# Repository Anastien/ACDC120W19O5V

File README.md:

19.5V 120W Universal Input AC Power Supply.

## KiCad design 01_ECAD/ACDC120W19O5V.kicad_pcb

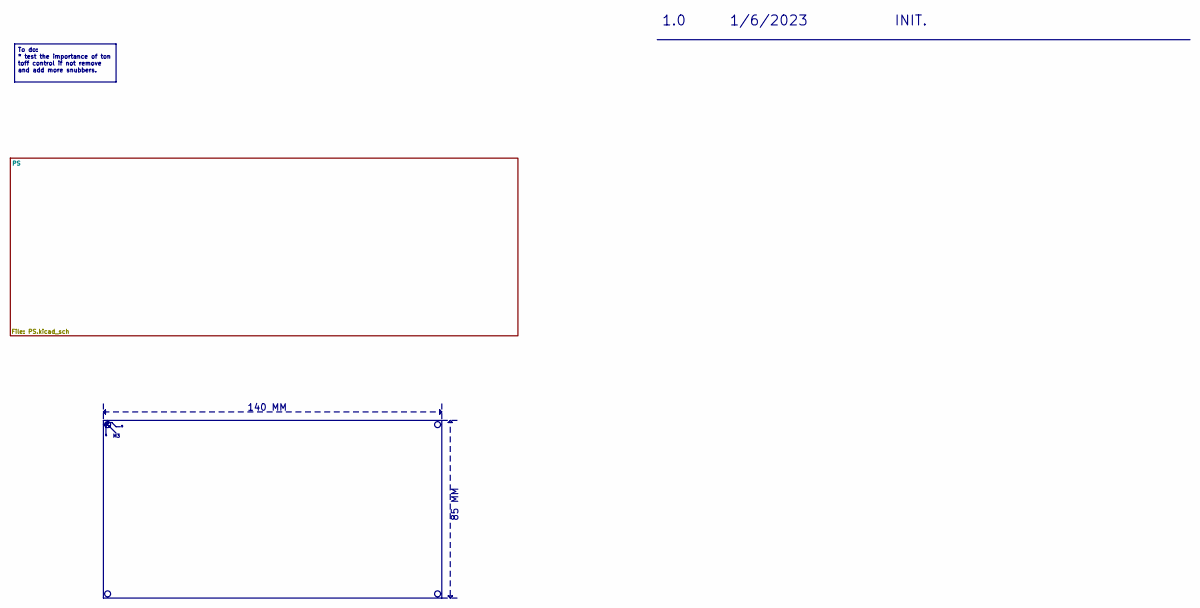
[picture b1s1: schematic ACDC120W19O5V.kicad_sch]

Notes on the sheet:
85 MM
1/6/2023
140 MM
1.0
INIT.
To do: * test the importance of ton toff control if not remove and add more snubbers.

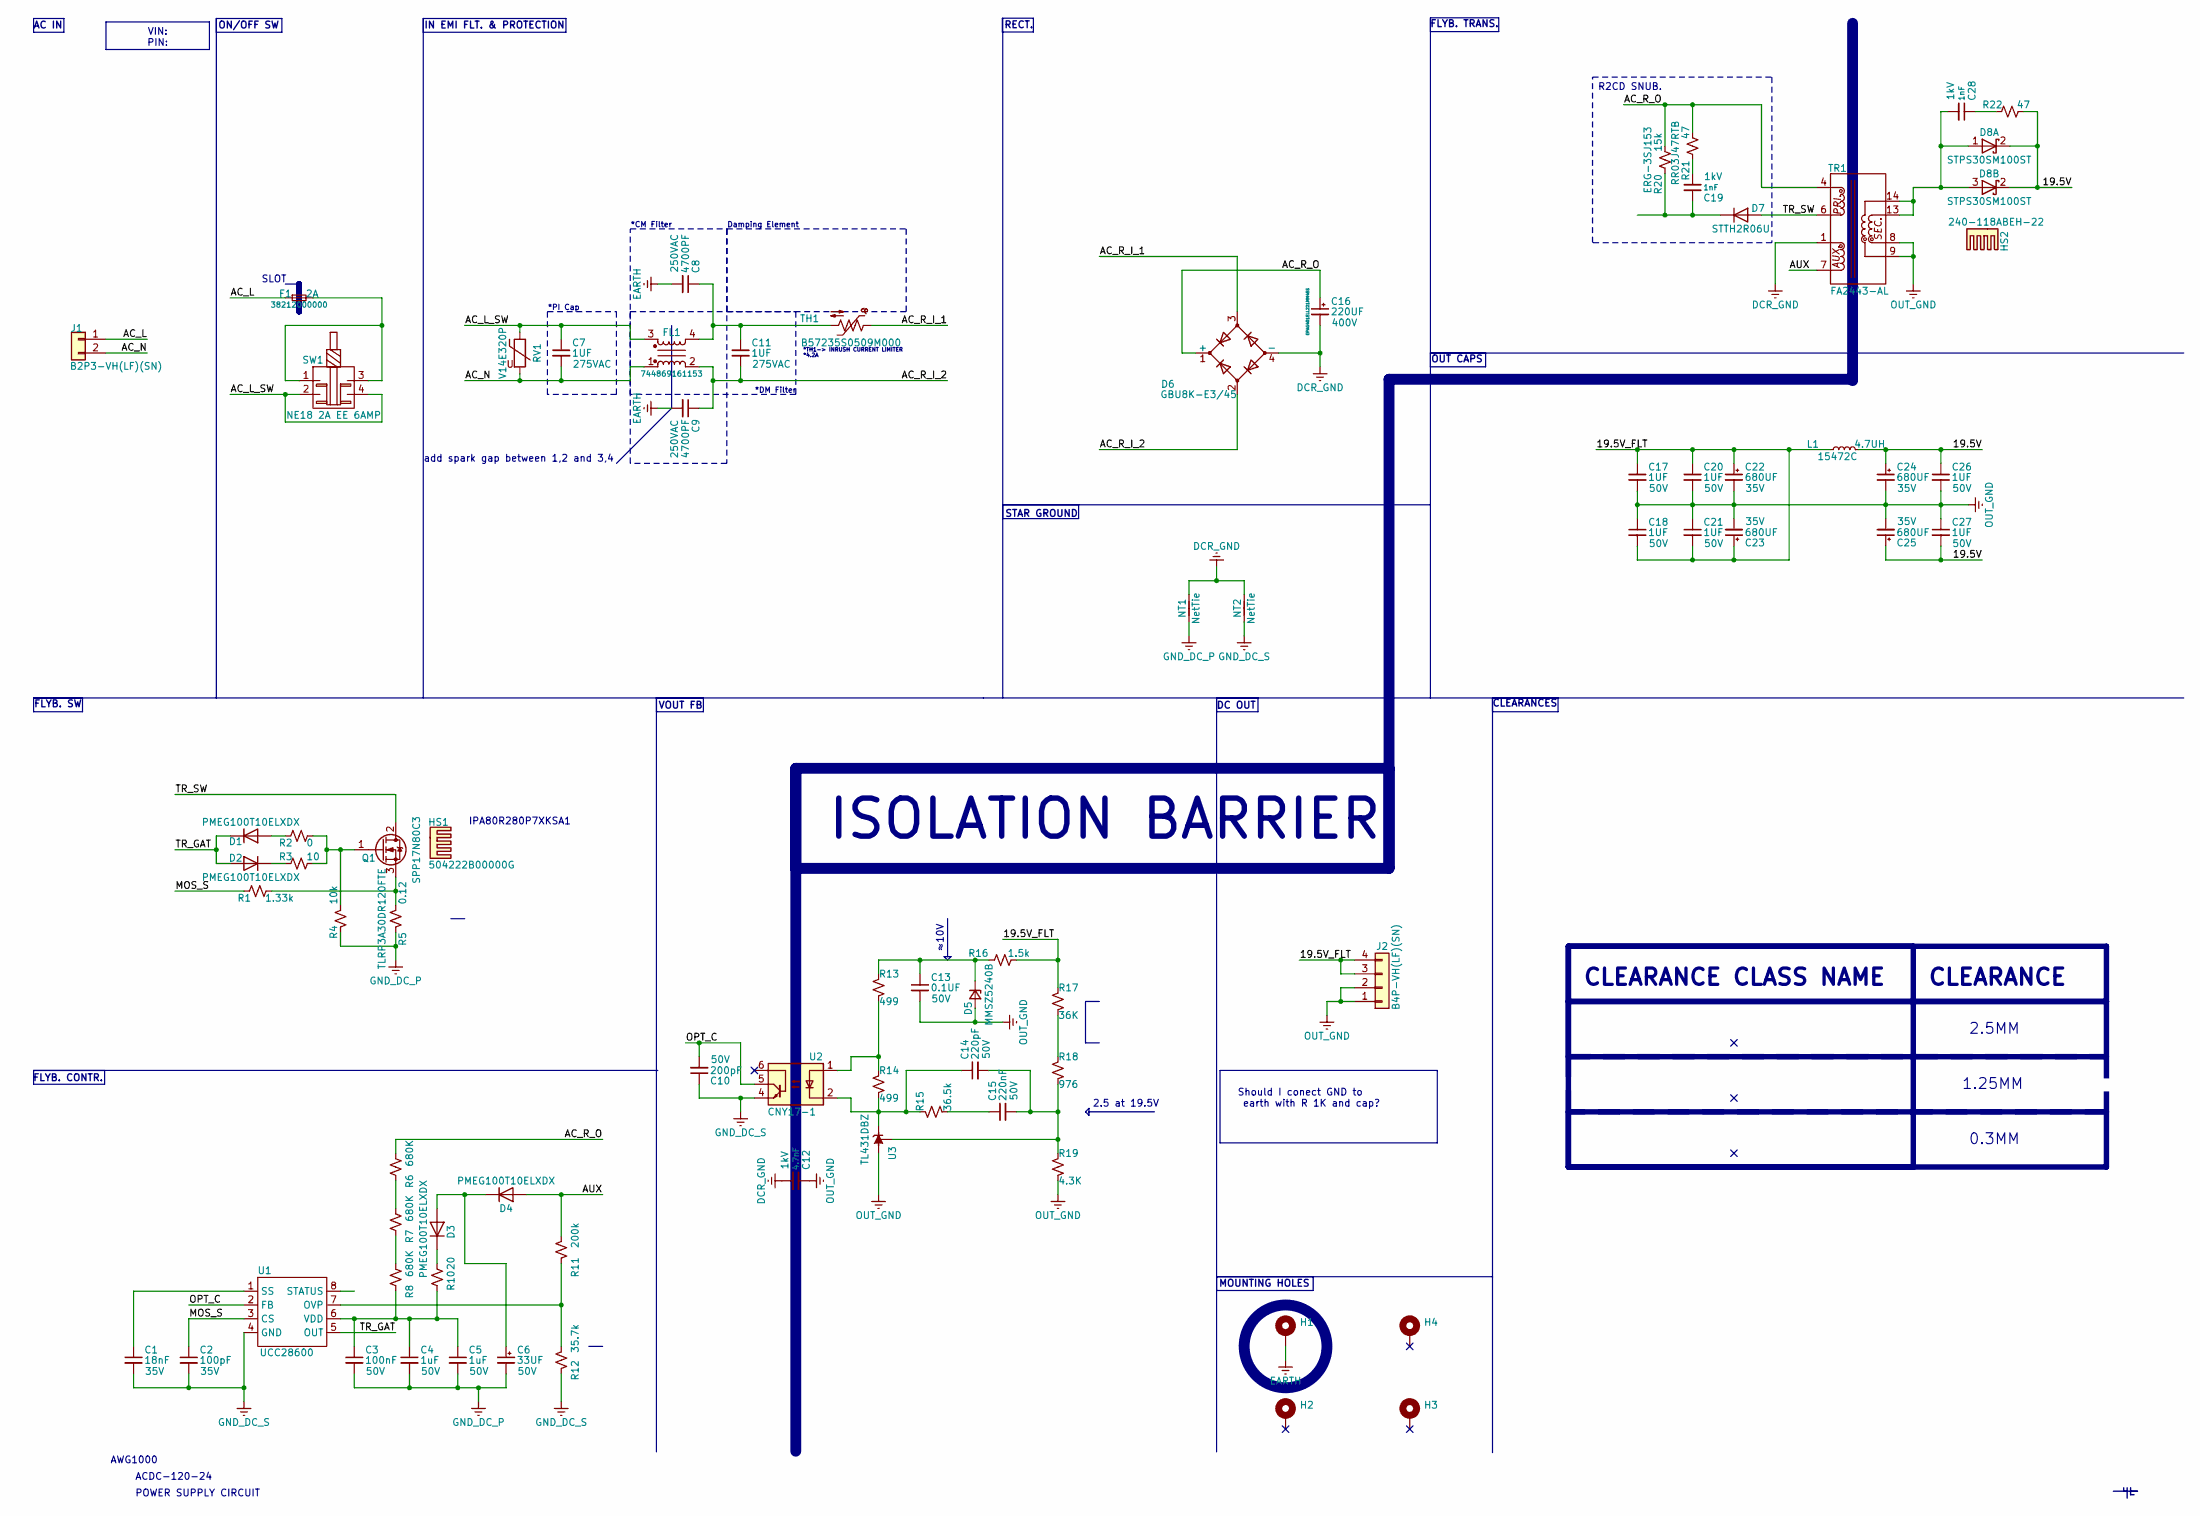
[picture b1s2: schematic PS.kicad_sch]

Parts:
C1: 18nF; C_0603_1608Metric; VOLTAGE 35V
C2: 100pF; C_0603_1608Metric; VOLTAGE 35V
C3: 100nF; C_0603_1608Metric; VOLTAGE 50V
C4, C5: 1uF; C_0603_1608Metric; VOLTAGE 50V
C6: 33UF; C_Radial_D6.3mm_H11.0mm_P2.50mm; VOLTAGE 50V
C7, C11: 1UF; 890324026027CS; VOLTAGE 275VAC
C8, C9: 4700PF; C_Disc_D10.5mm_W5.0mm_P5.00mm; VOLTAGE 250VAC
C10: 200pF; C_0603_1608Metric; VOLTAGE 50V
C12: 4.7nF; C_Disc_D7.5mm_W5.0mm_P7.50mm; VOLTAGE 1kV
C13: 0.1UF; C_0603_1608Metric; VOLTAGE 50V
C14: 220pF; C_0603_1608Metric; VOLTAGE 50V
C15: 220nF; C_0603_1608Metric; VOLTAGE 50V
C16: 220UF; CP_Radial_D18.0mm_P7.50mm; VOLTAGE 400V
C17, C18, C20, C21, C26, C27: 1UF; C_0805_2012Metric_Pad1.18x1.45mm_HandSolder; VOLTAGE 50V
C19, C28: 1nF; C_Disc_D7.5mm_W5.0mm_P7.50mm; VOLTAGE 1kV
C22, C23, C24, C25: 680UF; EKZN630ELL681MK30S; VOLTAGE 35V
D1, D2, D3, D4: PMEG100T10ELXDX; D_SOD-323
D5: MMSZ5240B; D_SOD-123F
D6: GBU8K-E3/45; Diode_Bridge_Vishay_GBU
D7: STTH2R06U; D_SMB
D8: STPS30SM100ST; TO-220-3-240
F1: 38212000000; 38211000410; Current Rating 2A
FL1: 744869161153
H1, H2, H3, H4: MountingHole_Pad; MountingHole_3.2mm_M3_DIN965_Pad_TopBottom
HS1: 504222B00000G
HS2: 240-118ABEH-22
J1: B2P3-VH(LF)(SN); JST_VH_B2P3-VH_1x02_P7.92mm_Vertical
J2: B4P-VH(LF)(SN); JST_VH_B4P-VH-B_1x04_P3.96mm_Vertical
L1: 4.7UH; 744750340047
NT1: NetTie; NetTie-2_SMD_Pad2.0mm
NT2: NetTie; NetTie-2_SMD_Pad0.5mm
Q1: SPP17N80C3; TO-220-3-240
R1: 1.33k; R_0603_1608Metric
R2: 0; R_0603_1608Metric
R3: 10; R_0603_1608Metric
R4: 10k; R_0603_1608Metric
R5: 0.12; R_2512_6332Metric_Pad1.40x3.35mm_HandSolder
R6, R7, R8: 680K; R_1206_3216Metric_Pad1.30x1.75mm_HandSolder
R10: 20; R_0603_1608Metric
R11: 200k; R_0603_1608Metric
R12: 35.7k; R_0603_1608Metric
R13, R14: 499; R_0603_1608Metric
R15: 36.5k; R_0603_1608Metric
R16: 1.5k; R_0603_1608Metric
R17: 36K; R_0603_1608Metric
R18: 976; R_0603_1608Metric
R19: 4.3K; R_0603_1608Metric
R20: 15k; R_Axial_DIN0516_L15.5mm_D5.0mm_P5.08mm_Vertical
R21, R22: 47; R_Axial_DIN0516_L15.5mm_D5.0mm_P5.08mm_Vertical
RV1: V14E320P; RV_Disc_D16.5mm_W6.7mm_P7.5mm
SW1: NE18 2A EE 6AMP; NE1846EE
TH1: B57235S0509M000; RV_Disc_D9mm_W6.1mm_P5mm
TR1: FA2443-AL
U1: UCC28600; SOIC-8_3.9x4.9mm_P1.27mm
U2: CNY17-1; DIP-6_W7.62mm_LongPads
U3: TL431DBZ; SOT-23

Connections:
/PS/19.5V: C24.1, C25.1, C26.1, C27.2, D8.2 (K), L1.2, R22.2
/PS/19.5V_FLT: C17.1, C18.2, C20.1, C21.2, C22.1, C23.1, J2.3, J2.4, L1.1, R16.2, R17.2
/PS/AC_L: F1.1, J1.1
/PS/AC_L_SW: C7.1, FL1.3, RV1.1, SW1.2, SW1.4
/PS/AC_N: C7.2, FL1.1, J1.2, RV1.2
/PS/AC_R_I_1: D6.3, TH1.1
/PS/AC_R_I_2: C9.1, C11.2, D6.2, FL1.2
/PS/AC_R_O: C16.1, D6.1 (+), R6.2, R20.2, R21.2, TR1.4
/PS/AUX: D4.2 (A), R11.2, TR1.7
/PS/MOS_S: C2.1, R1.2, U1.3 (CS)
/PS/OPT_C: C10.2, U1.2 (FB), U2.5
/PS/TR_GAT: D1.1 (K), D2.2 (A), U1.5 (OUT)
/PS/TR_SW: D7.2 (A), Q1.2 (D), TR1.6
DCR_GND: C12.2, C16.2, D6.4 (-), NT1.2, NT2.2, TR1.1
EARTH: C8.2, C9.2, H1.1
GND_DC_P: C3.2, C4.2, C5.2, C6.2, NT1.1, R4.2, R5.2
GND_DC_S: C1.2, C2.2, C10.1, NT2.1, R12.2, U1.4 (GND), U2.4
unnamed: C8.1, C11.1, FL1.4, TH1.2
unnamed: C15.1, R15.1
unnamed: C19.2, R21.1
unnamed: C28.1, R22.1
unnamed: D1.2 (A), R2.2
unnamed: D2.1 (K), R3.2
unnamed: C6.1, D3.2 (A), D4.1 (K)
unnamed: D3.1 (K), R10.1
unnamed: C13.1, D5.1 (K), R13.2, R16.1
unnamed: C19.1, D7.1 (K), R20.1
unnamed: C28.2, D8.1 (A), D8.3 (K), TR1.13, TR1.14
unnamed: F1.2, SW1.1, SW1.3
unnamed: Q1.1 (G), R2.1, R3.1, R4.1
unnamed: Q1.3 (S), R1.1, R5.1
unnamed: R6.1, R7.2
unnamed: R7.1, R8.2
unnamed: R13.1, R14.2, U2.1
unnamed: R17.1, R18.2
unnamed: R11.1, R12.1, U1.7 (OVP)
unnamed: C1.1, U1.1 (SS)
unnamed: C3.1, C4.1, C5.1, R8.1, R10.2, U1.6 (VDD)
unnamed: C14.1, R14.1, R15.2, U2.2, U3.1 (K)
unnamed: C14.2, C15.2, R18.1, R19.2, U3.2 (REF)
OUT_GND: C12.1, C13.2, C17.2, C18.1, C20.2, C21.1, C22.2, C23.2, C24.2, C25.2, C26.2, C27.1, D5.2 (A), J2.1, J2.2, R19.1, TR1.8, TR1.9, U3.3 (A)

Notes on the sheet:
CLEARANCE CLASS NAME
MOUNTING HOLES
2.5MM
OUT CAPS
RECT.
VOUT FB
POWER SUPPLY CIRCUIT
IN EMI FLT. & PROTECTION
AC IN
1.25MM
CLEARANCE
2.5 at 19.5V
*PI Cap
Damping Element
add spark gap between 1,2 and 3,4
FLYB. CONTR.
*4.2A
CLEARANCES
≈10V
IPA80R280P7XKSA1
AWG1000
*CM Filter
Should I conect GND to earth with R 1K and cap?
FLYB. TRANS.
ACDC-120-24
*DM Filter
*TH1-> INRUSH CURRENT LIMITER
DC OUT
STAR GROUND
ON/OFF SW
ISOLATION BARRIER
0.3MM
FLYB. SW
SLOT
R2CD SNUB.
VIN: PIN:

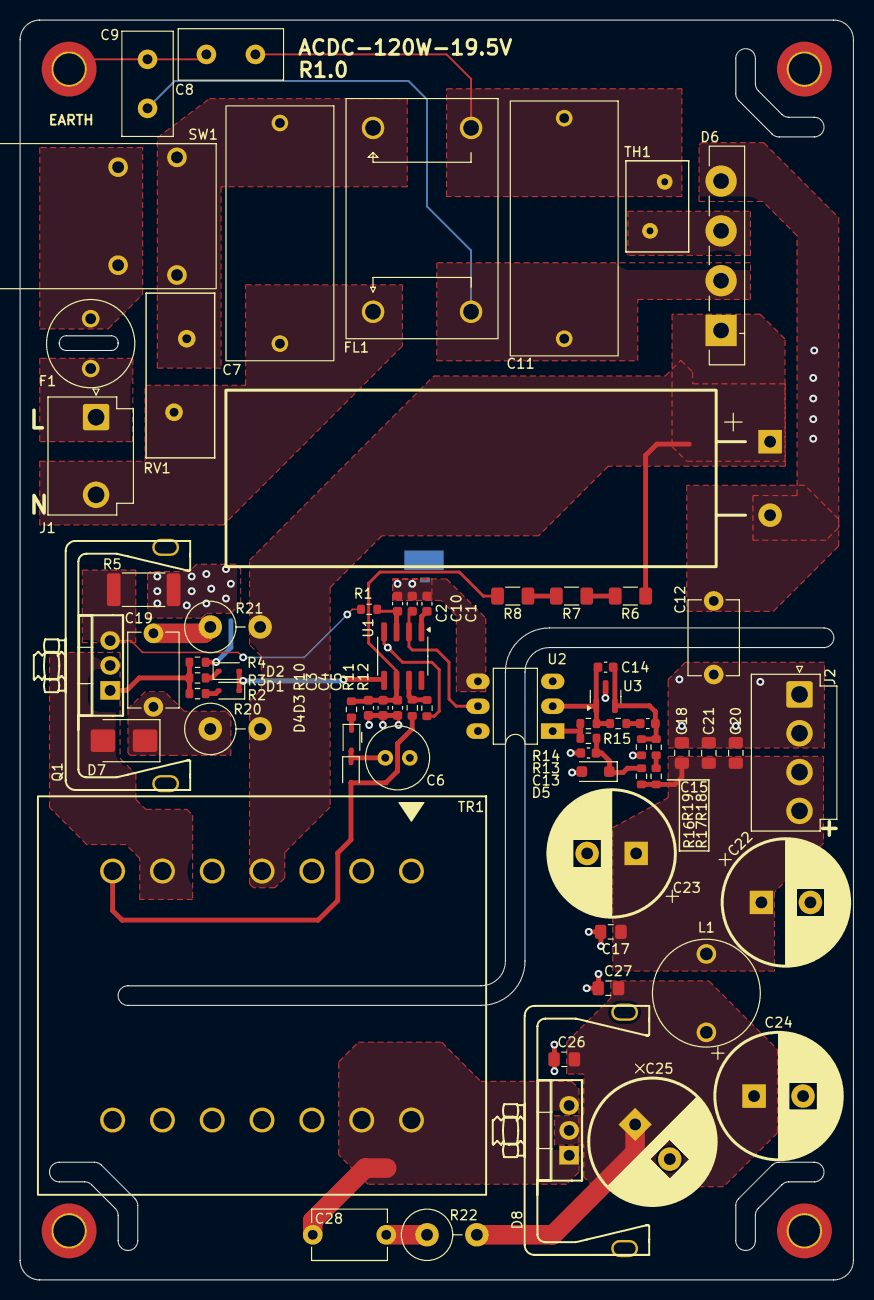
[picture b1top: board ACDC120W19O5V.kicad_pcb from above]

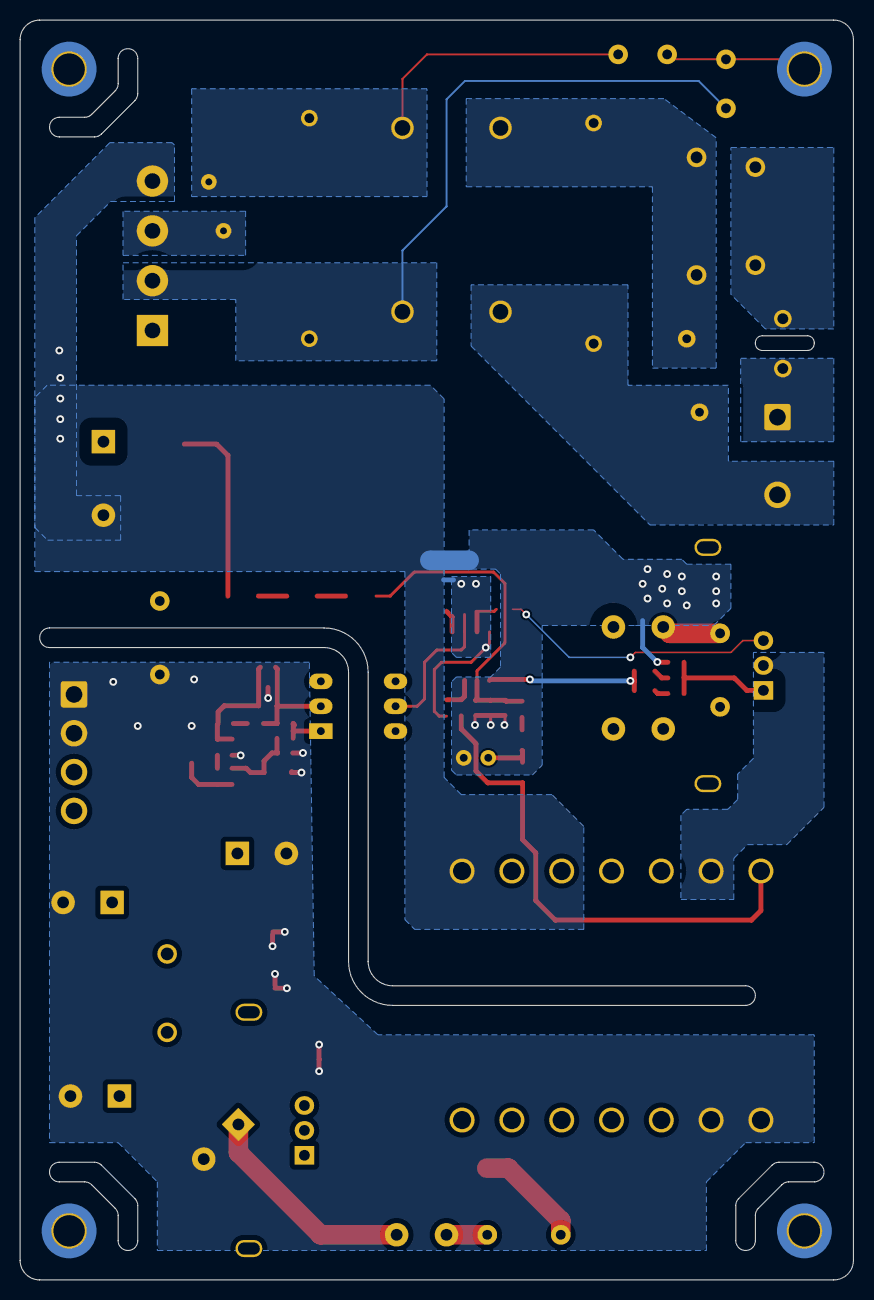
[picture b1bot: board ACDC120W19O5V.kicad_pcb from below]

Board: 2 copper layers, 85.0 x 128.5 mm, 76 parts (3 on the bottom side), 41 nets.

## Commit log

2024-10-27 Init.
